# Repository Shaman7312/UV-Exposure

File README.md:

# UV-Exposure
Exposure unit for making PCBs

***Software isn't working yet***

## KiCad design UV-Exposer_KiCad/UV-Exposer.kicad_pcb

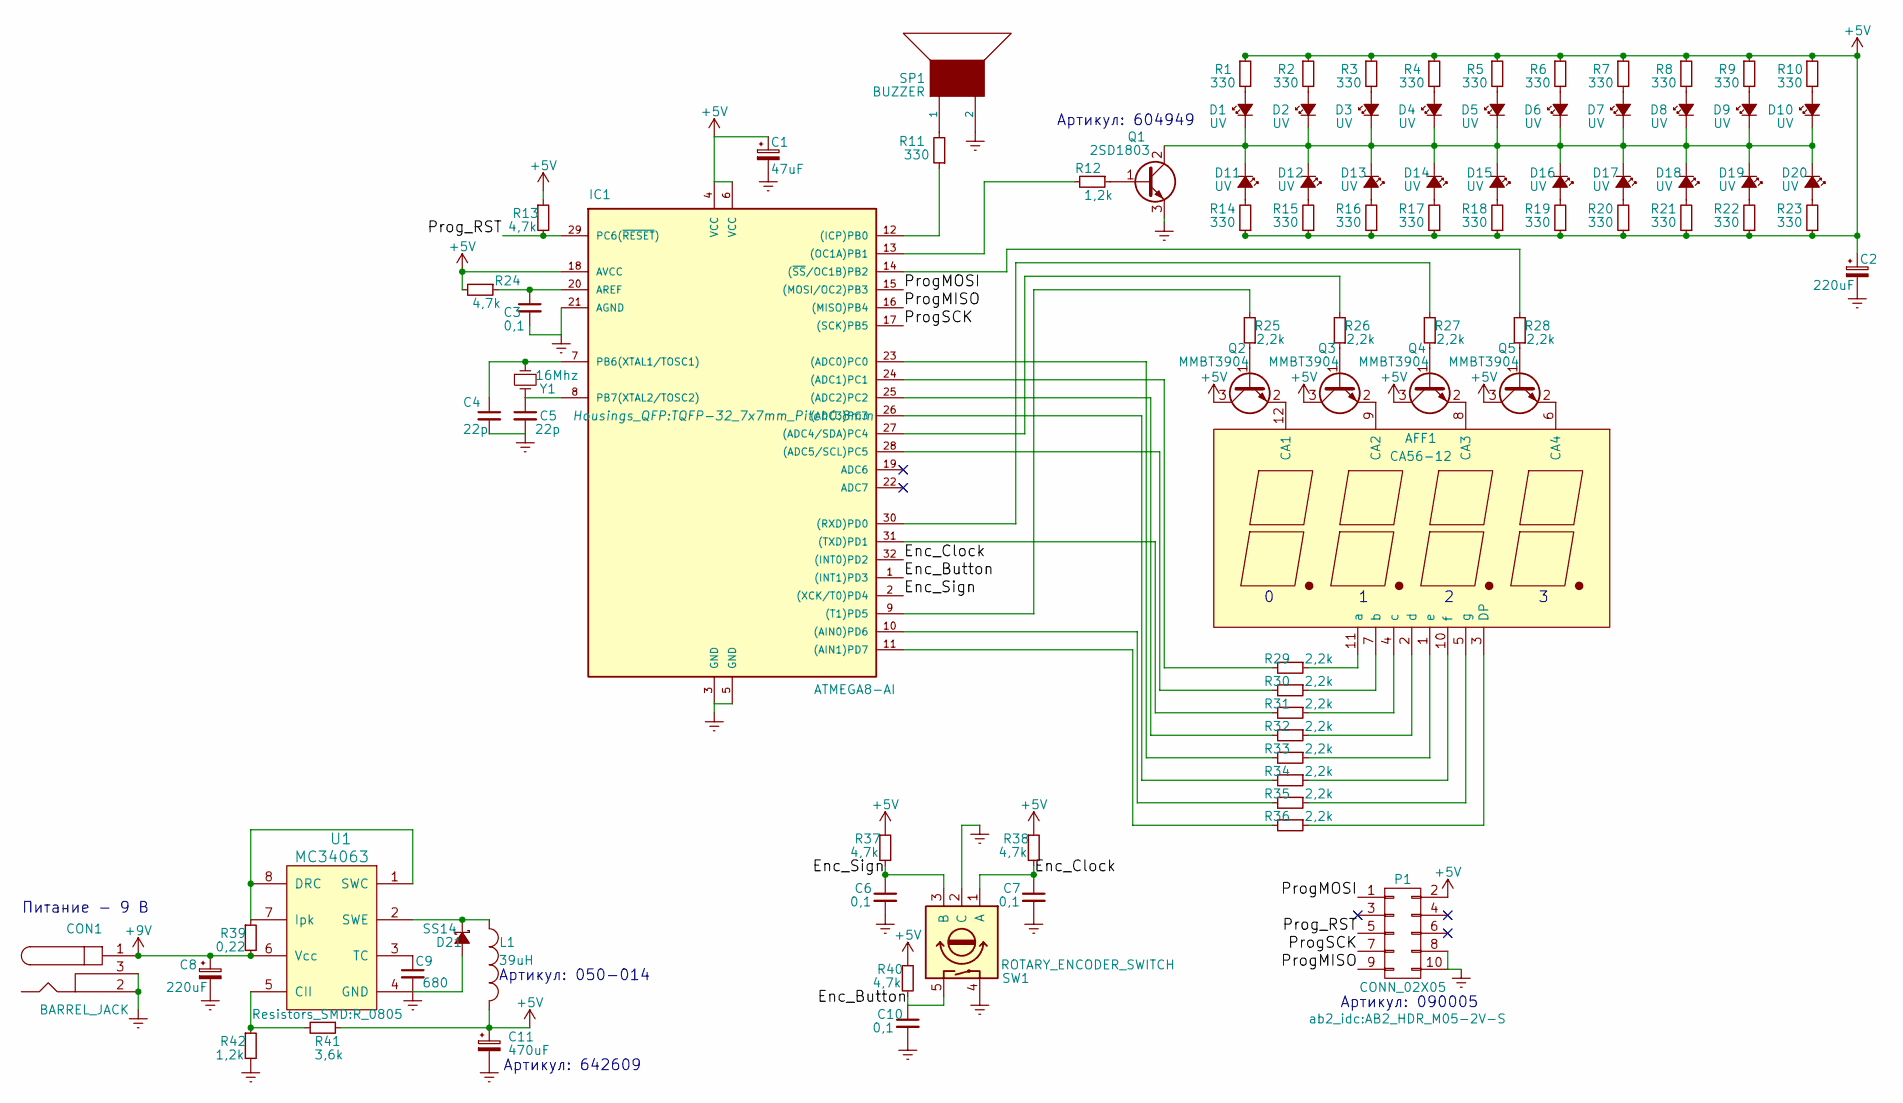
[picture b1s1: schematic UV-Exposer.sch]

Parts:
AFF1: CA56-12; CA56-12CGKWA
C1: 47uF; CP_Elec_5x5.3
C2, C8: 220uF; CP_Elec_6.3x5.3
C3, C6, C7, C10: 0,1; C_1206
C4, C5: 22p; C_1206
C9: 680; C_1206
C11: 470uF; CP_Elec_8x10
CON1: BARREL_JACK
D1, D2, D3, D4, D5, D6, D7, D8, D9, D10, D11, D12, D13, D14, D15, D16, D17, D18, D19, D20: UV; LED_D5.0mm
D21: SS14; D_SMA
IC1: ATMEGA8-AI; TQFP-32_7x7mm_Pitch0.8mm
L1: 39uH; Choke_SMD_12x12mm_h8mm
P1: CONN_02X05; AB2_HDR_M05-2V-S
Q1: 2SD1803; TO-252-2
Q2, Q3, Q4, Q5: MMBT3904; SOT-23
R1, R2, R3, R4, R5, R6, R7, R8, R9, R10, R11, R14, R15, R16, R17, R18, R19, R20, R21, R22, R23: 330; R_0805
R12: 1,2k; R_1206
R13, R24, R37, R38, R40: 4,7k; R_1206
R25, R26, R27, R28, R29, R30, R31, R32, R33, R34, R35, R36: 2,2k; R_1206
R39: 0,22; R_Axial_DIN0414_L11.9mm_D4.5mm_P15.24mm_Horizontal
R41: 3,6k; R_0805
R42: 1,2k; R_0805
SP1: BUZZER; MagneticBuzzer_ProSignal_ABI-009-RC
SW1: ROTARY_ENCODER_SWITCH; AB2_ROTARY_ENCODER_W_SWITCH
U1: MC34063; SOIC-8_3.9x4.9mm_Pitch1.27mm
Y1: 16Mhz; Crystal_HC49-U_Vertical

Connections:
+5V: C1.1, C2.1, C11.1, IC1.4 (VCC), IC1.6 (VCC), IC1.18 (AVCC), L1.2, P1.2, Q2.3 (C), Q3.3 (C), Q4.3 (C), Q5.3 (C), R1.1, R2.1, R3.1, R4.1, R5.1, R6.1, R7.1, R8.1, R9.1, R10.1, R13.1, R14.1, R15.1, R16.1, R17.1, R18.1, R19.1, R20.1, R21.1, R22.1, R23.1, R24.2, R37.1, R38.1, R40.1, R41.1
+9V: C8.1, CON1.1, R39.2, U1.6 (Vcc)
/Enc_Button: C10.1, IC1.1 ((INT1)PD3), R40.2, SW1.5
/Enc_Clock: C7.1, IC1.32 ((INT0)PD2), R38.2, SW1.1 (A)
/Enc_Sign: C6.1, IC1.2 ((XCK/T0)PD4), R37.2, SW1.3 (B)
/ProgMISO: IC1.16 ((MISO)PB4), P1.9
/ProgMOSI: IC1.15 ((MOSI/OC2)PB3), P1.1
/ProgSCK: IC1.17 ((SCK)PB5), P1.7
/Prog_RST: IC1.29 (PC6(~RESET~)), P1.5, R13.2
Earth: C1.2, C2.2, C3.2, C4.2, C5.2, C6.2, C7.2, C8.2, C9.2, C10.2, C11.2, CON1.2, CON1.3, D21.2 (A), IC1.3 (GND), IC1.5 (GND), IC1.21 (AGND), P1.8, P1.10, Q1.3 (E), R42.2, SP1.2, SW1.2 (C), SW1.4, U1.4 (GND)
unnamed: AFF1.1 (e), R33.1
unnamed: AFF1.2 (d), R32.1
unnamed: AFF1.3 (DP), R36.1
unnamed: AFF1.4 (c), R31.1
unnamed: AFF1.5 (g), R35.1
unnamed: AFF1.6 (CA4), Q5.2 (E)
unnamed: AFF1.7 (b), R30.1
unnamed: AFF1.8 (CA3), Q4.2 (E)
unnamed: AFF1.9 (CA2), Q3.2 (E)
unnamed: AFF1.10 (f), R34.1
unnamed: AFF1.11 (a), R29.1
unnamed: AFF1.12 (CA1), Q2.2 (E)
unnamed: C3.1, IC1.20 (AREF), R24.1
unnamed: C4.1, IC1.7 (PB6(XTAL1/TOSC1)), Y1.1
unnamed: C5.1, IC1.8 (PB7(XTAL2/TOSC2)), Y1.2
unnamed: C9.1, U1.3 (TC)
unnamed: D1.1 (K), D2.1 (K), D3.1 (K), D4.1 (K), D5.1 (K), D6.1 (K), D7.1 (K), D8.1 (K), D9.1 (K), D10.1 (K), D11.1 (K), D12.1 (K), D13.1 (K), D14.1 (K), D15.1 (K), D16.1 (K), D17.1 (K), D18.1 (K), D19.1 (K), D20.1 (K), Q1.2 (C)
unnamed: D1.2 (A), R1.2
unnamed: D2.2 (A), R2.2
unnamed: D3.2 (A), R3.2
unnamed: D4.2 (A), R4.2
unnamed: D5.2 (A), R5.2
unnamed: D6.2 (A), R6.2
unnamed: D7.2 (A), R7.2
unnamed: D8.2 (A), R8.2
unnamed: D9.2 (A), R9.2
unnamed: D10.2 (A), R10.2
unnamed: D11.2 (A), R14.2
unnamed: D12.2 (A), R15.2
unnamed: D13.2 (A), R16.2
unnamed: D14.2 (A), R17.2
unnamed: D15.2 (A), R18.2
unnamed: D16.2 (A), R19.2
unnamed: D17.2 (A), R20.2
unnamed: D18.2 (A), R21.2
unnamed: D19.2 (A), R22.2
unnamed: D20.2 (A), R23.2
unnamed: D21.1 (K), L1.1, U1.2 (SWE)
unnamed: IC1.9 ((T1)PD5), R25.2
unnamed: IC1.10 ((AIN0)PD6), R35.2
unnamed: IC1.11 ((AIN1)PD7), R36.2
unnamed: IC1.12 ((ICP)PB0), R11.1
unnamed: IC1.13 ((OC1A)PB1), R12.2
unnamed: IC1.14 ((~SS~/OC1B)PB2), R28.2
unnamed: IC1.23 ((ADC0)PC0), R33.2
unnamed: IC1.24 ((ADC1)PC1), R29.2
unnamed: IC1.25 ((ADC2)PC2), R32.2
unnamed: IC1.26 ((ADC3)PC3), R34.2
unnamed: IC1.27 ((ADC4/SDA)PC4), R26.2
unnamed: IC1.28 ((ADC5/SCL)PC5), R30.2
unnamed: IC1.30 ((RXD)PD0), R27.2
unnamed: IC1.31 ((TXD)PD1), R31.2
unnamed: Q1.1 (B), R12.1
unnamed: Q2.1 (B), R25.1
unnamed: Q3.1 (B), R26.1
unnamed: Q4.1 (B), R27.1
unnamed: Q5.1 (B), R28.1
unnamed: R11.2, SP1.1
unnamed: R39.1, U1.1 (SWC), U1.7 (Ipk), U1.8 (DRC)
unnamed: R41.2, R42.1, U1.5 (CII)

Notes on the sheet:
Питание - 9 В
Артикул: 050-014
Артикул: 604949
Артикул: 090005
Артикул: 642609

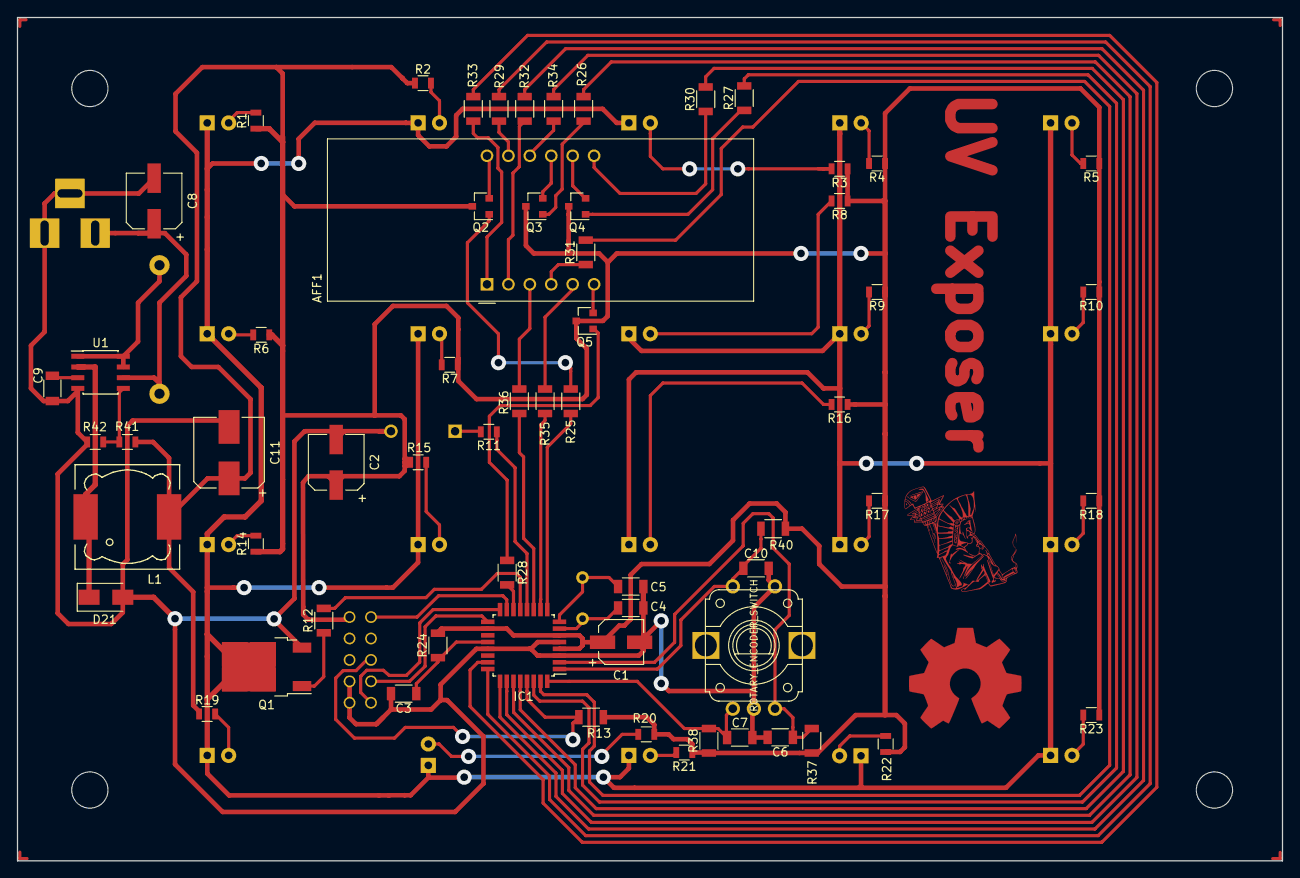
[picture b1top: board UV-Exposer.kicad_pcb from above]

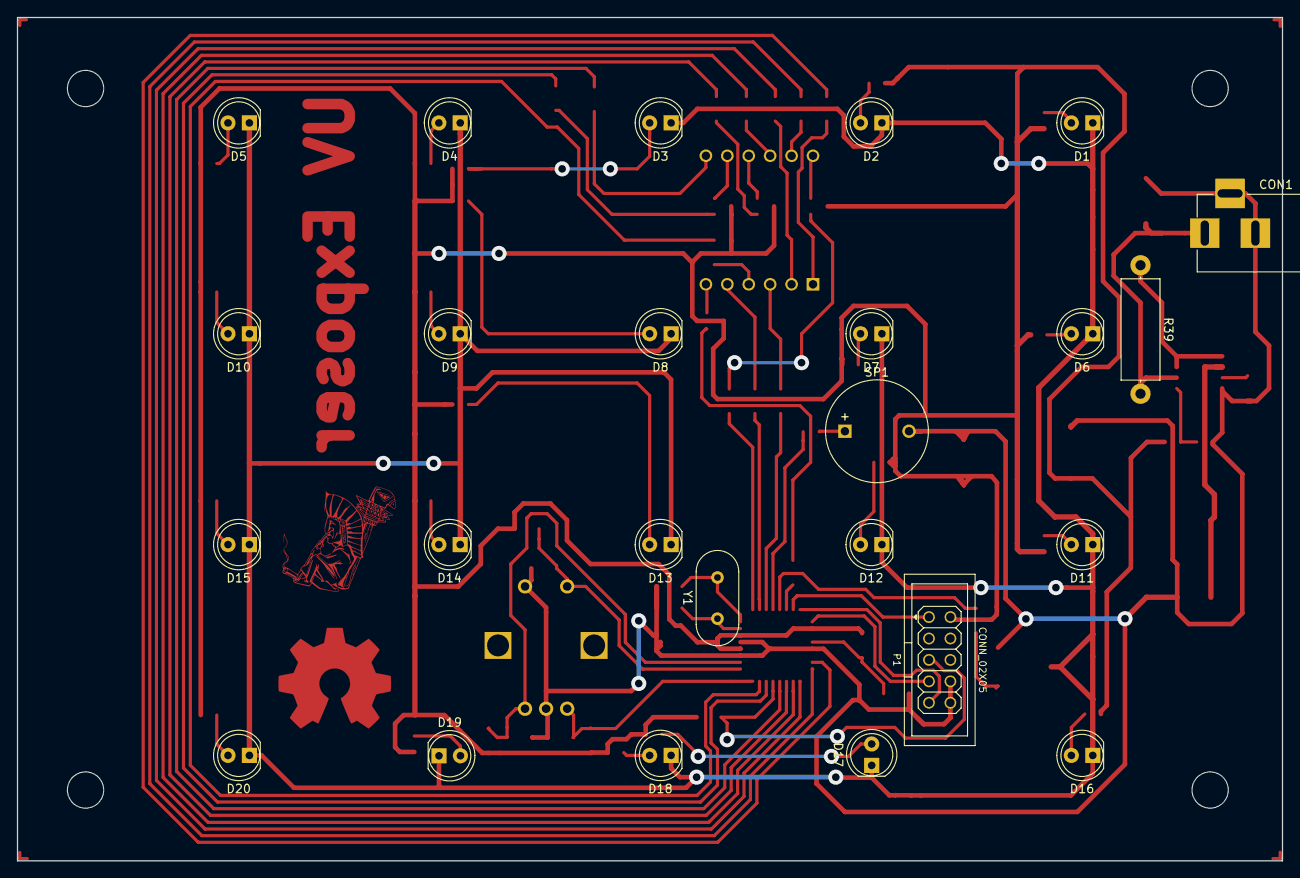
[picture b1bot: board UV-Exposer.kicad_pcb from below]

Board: 2 copper layers, 150.0 x 100.0 mm, 89 parts (25 on the bottom side), 70 nets.

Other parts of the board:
Shaman: Shaman_LOGO; shaman_logo13x13
